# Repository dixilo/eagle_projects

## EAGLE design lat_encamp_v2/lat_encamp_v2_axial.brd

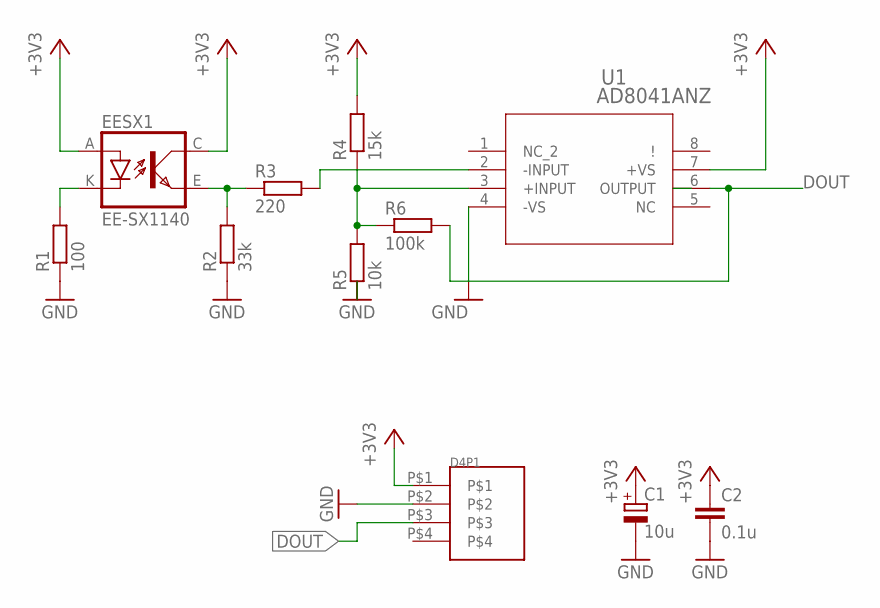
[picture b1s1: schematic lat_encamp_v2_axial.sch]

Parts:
C1: 10u; E2,5-6E
C2: 0.1u; C050-024X044
D4P1: DF1E-4P
EESX1: EE-SX1140
R1: 100; 0204/7
R2: 33k; 0204/7
R3: 220; 0204/7
R4: 15k; 0204/7
R5: 10k; 0204/7
R6: 100k; 0204/7
U1: AD8041ANZ; N_8_ADI

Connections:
+3V3: C1.+, C2.1, D4P1.P$1, EESX1.A, EESX1.C (COL), R4.2, U1.7 (+VS)
DOUT: D4P1.P$3, R6.2, U1.6 (OUTPUT)
GND: C1.-, C2.2, D4P1.P$2, R1.1, R2.1, R5.1, U1.4 (-VS)
unnamed: R3.2, U1.2 (-INPUT)
unnamed: R4.1, R5.2, R6.1, U1.3 (+INPUT)
unnamed: EESX1.E (EMIT), R2.2, R3.1
unnamed: EESX1.K (C), R1.2

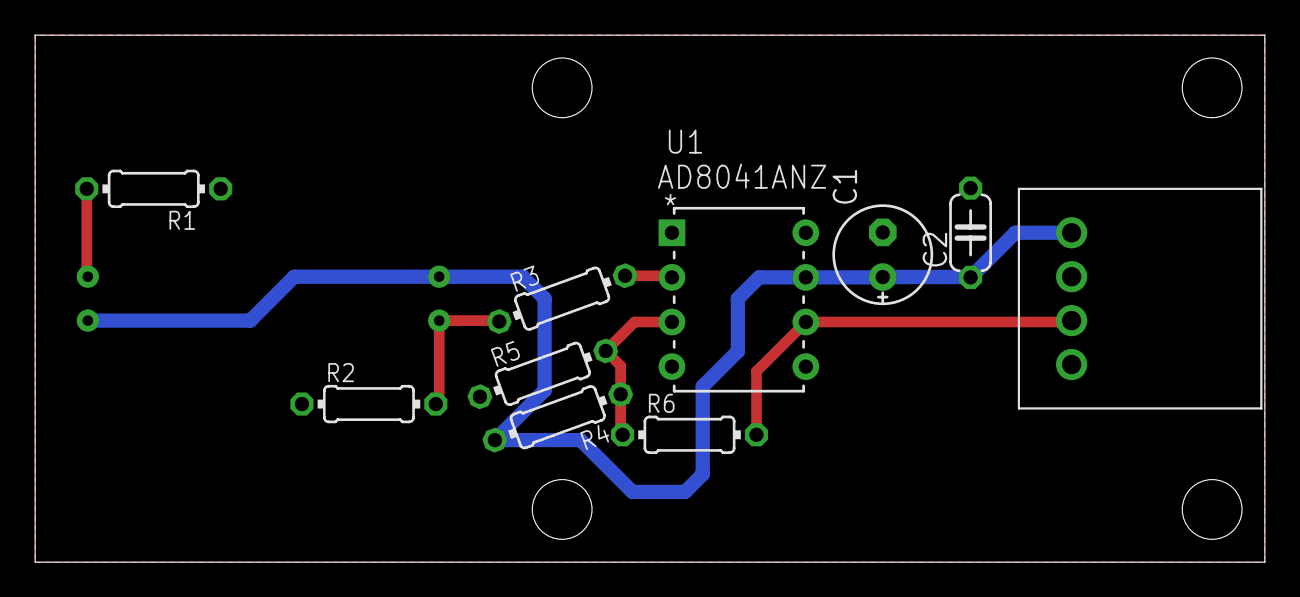
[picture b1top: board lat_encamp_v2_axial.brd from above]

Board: 2 copper layers, 70.0 x 30.0 mm, 11 parts (1 on the bottom side), 7 nets.

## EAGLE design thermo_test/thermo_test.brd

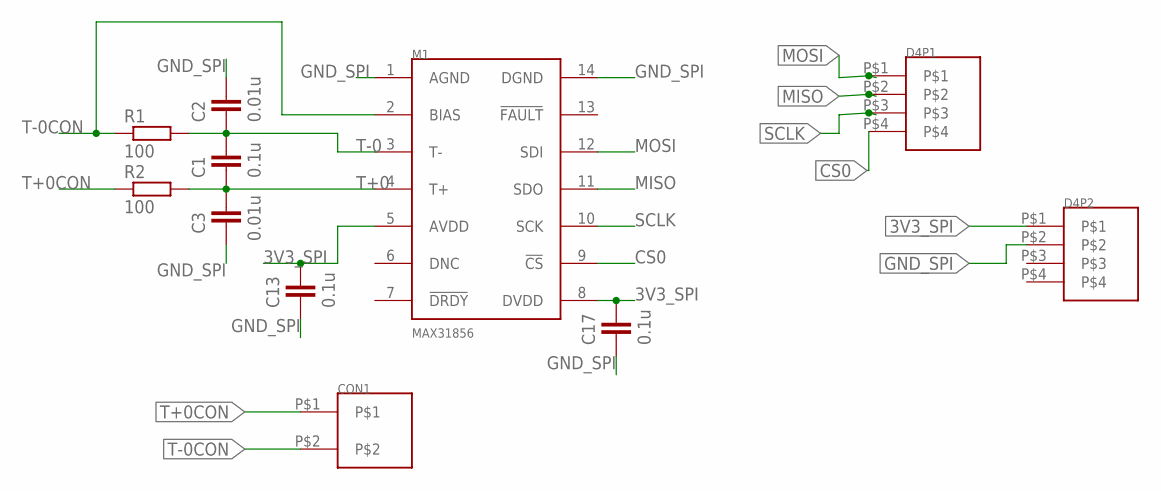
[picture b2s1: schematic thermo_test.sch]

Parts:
C1, C13, C17: 0.1u; C0603
C2, C3: 0.01u; C0603
CON1: 893-1332
D4P1, D4P2: DF1E-4P
M1: MAX31856; TSSOP14
R1, R2: 100; R0603

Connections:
3V3_SPI: C13.1, C17.1, D4P2.P$1, M1.5 (AVDD), M1.8 (DVDD)
CS0: D4P1.P$4, M1.9 (!CS)
GND_SPI: C2.1, C3.2, C13.2, C17.2, D4P2.P$2, M1.1 (AGND), M1.14 (DGND)
MISO: D4P1.P$2, M1.11 (SDO)
MOSI: D4P1.P$1, M1.12 (SDI)
SCLK: D4P1.P$3, M1.10 (SCK)
T+0: C1.2, C3.1, M1.4 (T+), R2.2
T+0CON: CON1.P$1, R2.1
T-0: C1.1, C2.2, M1.3 (T-), R1.2
T-0CON: CON1.P$2, M1.2 (BIAS), R1.1

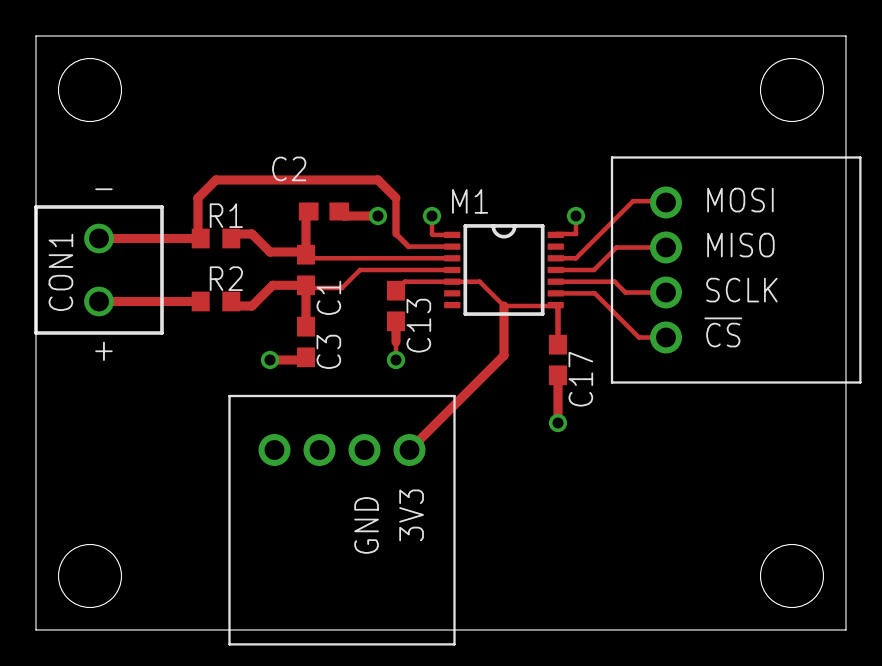
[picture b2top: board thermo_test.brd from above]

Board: 2 copper layers, 45.0 x 33.0 mm, 11 parts (0 on the bottom side), 10 nets.

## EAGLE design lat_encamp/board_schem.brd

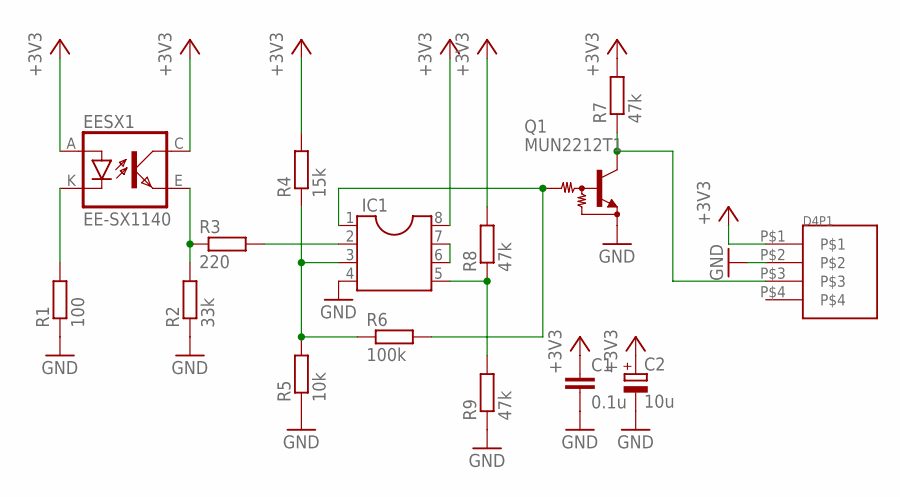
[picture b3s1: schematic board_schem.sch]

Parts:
C1: 0.1u; C050-024X044
C2: 10u; E2,5-5
D4P1: DF1E-4P
EESX1: EE-SX1140
IC1: DIL8; DIL08
Q1: MUN2212T1; SC59-BEC
R1: 100; 0207/10
R2: 33k; 0207/10
R3: 220; 0207/10
R4: 15k; 0207/10
R5: 10k; 0207/10
R6: 100k; 0207/10
R7, R8, R9: 47k; 0207/10

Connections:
+3V3: C1.1, C2.+, D4P1.P$1, EESX1.A, EESX1.C (COL), IC1.8, R4.2, R7.2, R8.2
GND: C1.2, C2.-, D4P1.P$2, IC1.4, Q1.E, R1.1, R2.1, R5.1, R9.1
unnamed: EESX1.K (C), R1.2
unnamed: EESX1.E (EMIT), R2.2, R3.1
unnamed: IC1.2, R3.2
unnamed: IC1.1, Q1.B, R6.2
unnamed: D4P1.P$3, Q1.C, R7.1
unnamed: IC1.3, R4.1, R5.2, R6.1
unnamed: IC1.6, IC1.7
unnamed: IC1.5, R8.1, R9.2

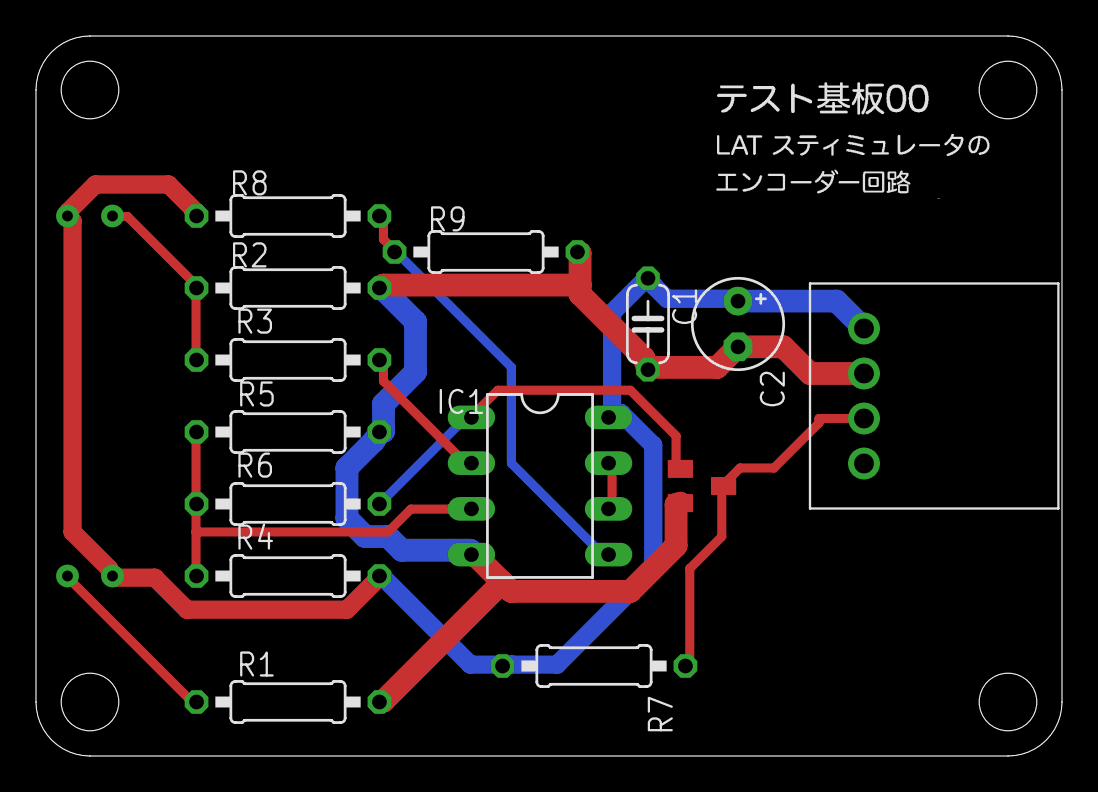
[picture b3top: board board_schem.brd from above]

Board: 2 copper layers, 57.0 x 40.0 mm, 15 parts (1 on the bottom side), 10 nets.

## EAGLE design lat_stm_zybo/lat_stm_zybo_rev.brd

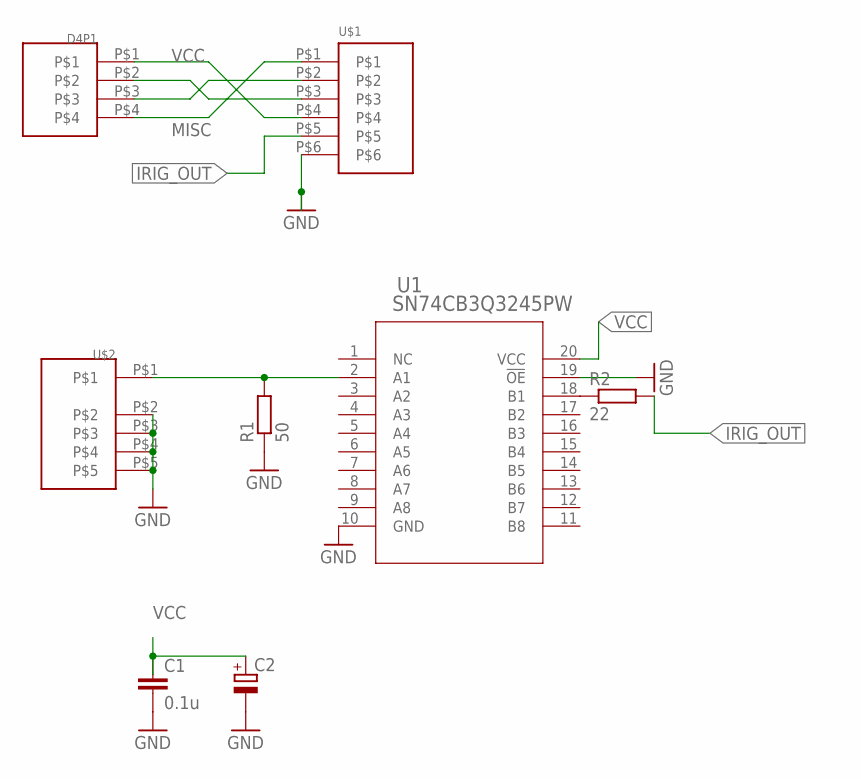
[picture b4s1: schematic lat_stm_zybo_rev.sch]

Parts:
C1: 0.1u; C0603
C2: CPOL-EUE2,5-6E; E2,5-6E
D4P1: DF1E-4P
R1: 50; R0603
R2: 22; R0603
U1: SN74CB3Q3245PW; PW20
U$1: DF1E-6P
U$2: 546-4049

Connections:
GND: C1.2, C2.-, R1.1, U1.10 (GND), U1.19 (!OE), U$1.P$6, U$2.P$2, U$2.P$3, U$2.P$4, U$2.P$5
IRIG_IN: R1.2, U1.2 (A1), U$2.P$1
IRIG_OUT: R2.2, U$1.P$5
MISC: D4P1.P$4, U$1.P$1
unnamed: R2.1, U1.18 (B1)
unnamed: D4P1.P$2, U$1.P$3
unnamed: D4P1.P$3, U$1.P$2
VCC: C1.1, C2.+, D4P1.P$1, U1.20 (VCC), U$1.P$4

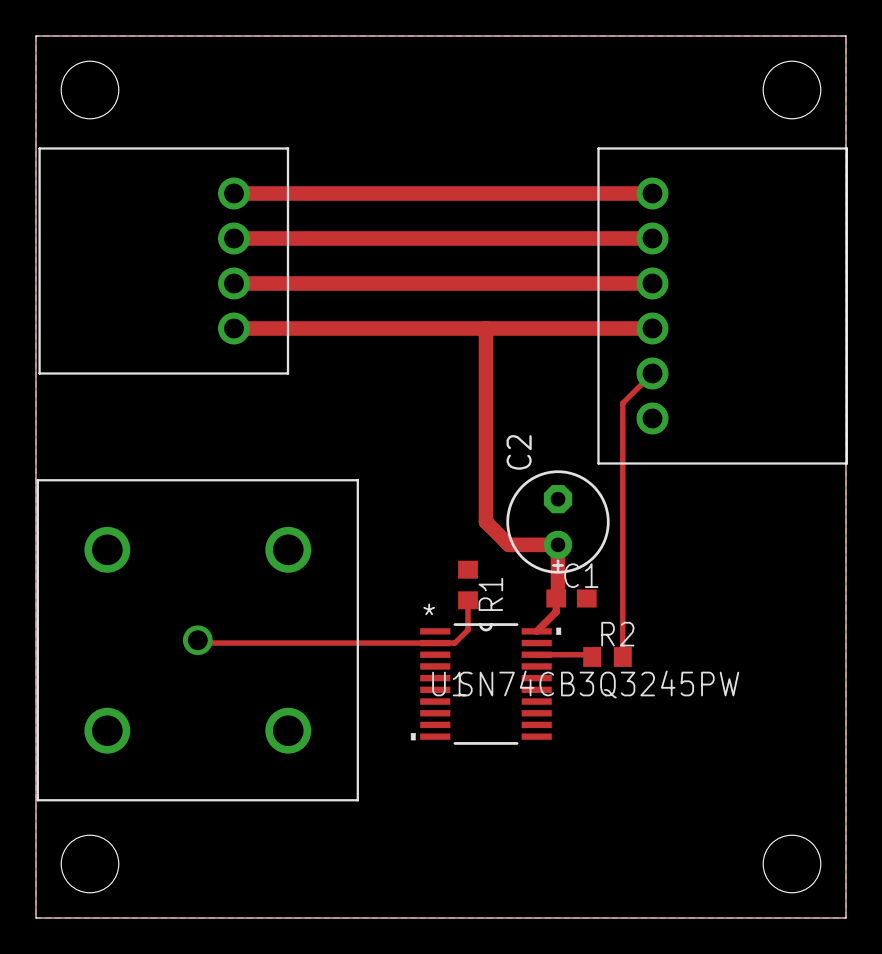
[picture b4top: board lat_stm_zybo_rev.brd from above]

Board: 2 copper layers, 45.0 x 49.0 mm, 8 parts (0 on the bottom side), 8 nets.

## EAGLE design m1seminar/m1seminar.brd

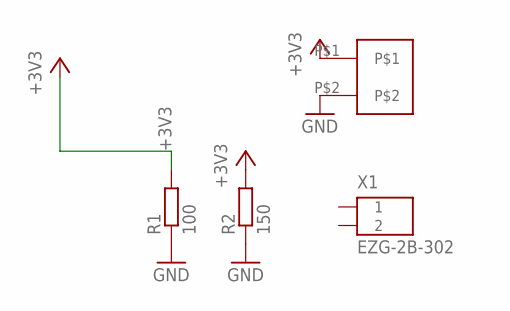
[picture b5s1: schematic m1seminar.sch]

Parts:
R1: 100; 0204/7
R2: 150; 0204/7
U$1: DF1E-2P
X1: EZG-2B-302; EZG-2B-2K-302

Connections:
+3V3: R1.2, R2.2, U$1.P$1
GND: R1.1, R2.1, U$1.P$2

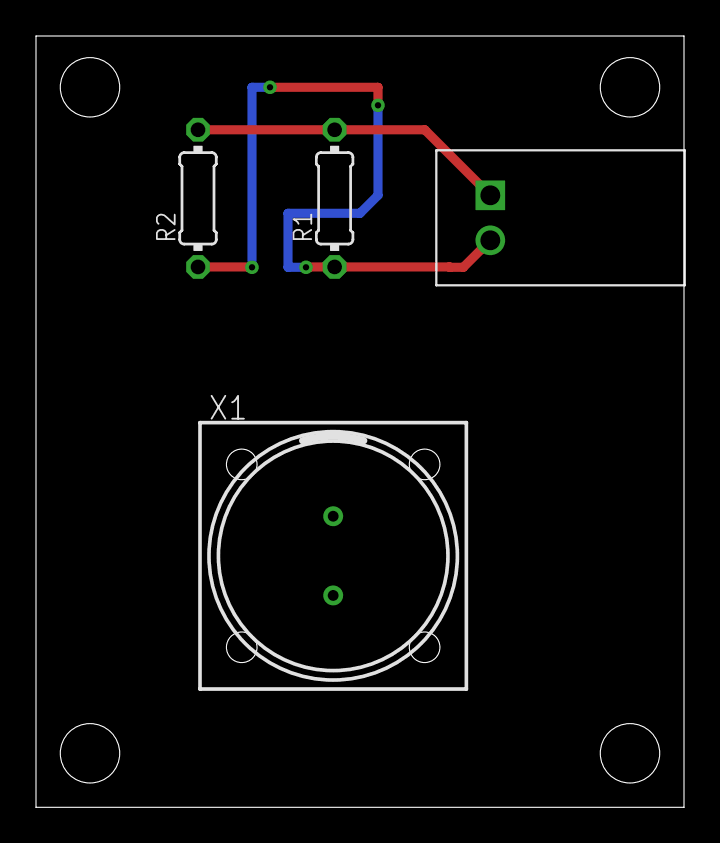
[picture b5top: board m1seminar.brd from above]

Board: 2 copper layers, 36.0 x 42.9 mm, 4 parts (0 on the bottom side), 2 nets.

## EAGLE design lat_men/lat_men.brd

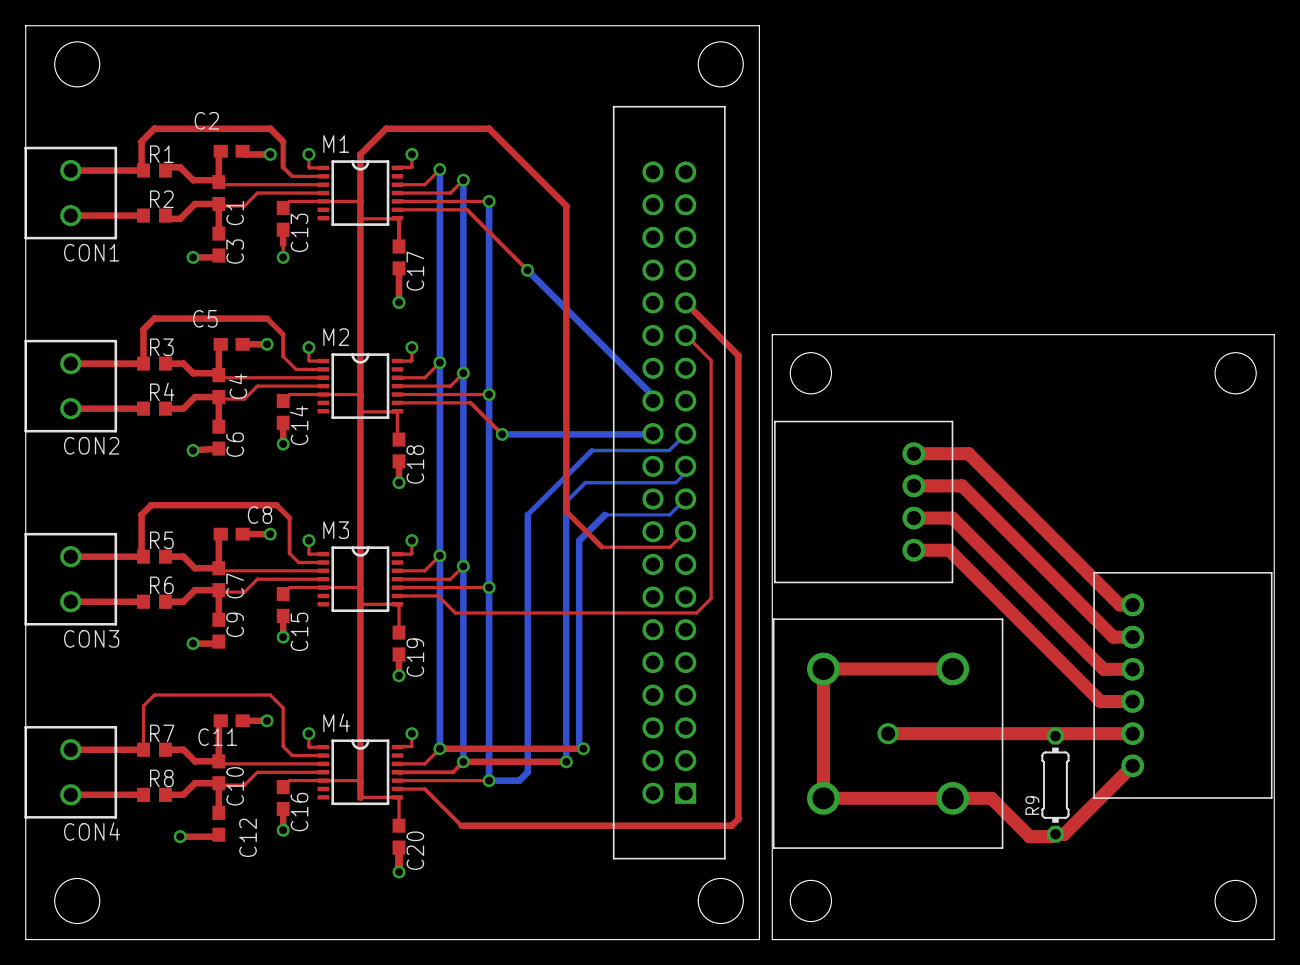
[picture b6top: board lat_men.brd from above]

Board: 2 copper layers, 97.0 x 71.0 mm, 41 parts (0 on the bottom side), 31 nets.

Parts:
C1, C4, C7, C10, C13, C14, C15, C16, C17, C18, C19, C20: 0.1u; C0603
C2, C3, C5, C6, C8, C9, C11, C12: 0.01u; C0603
CON1, CON2, CON3, CON4: 893-1332
D4P1: DF1E-4P
M1, M2, M3, M4: MAX31856; TSSOP14
R1, R2, R3, R4, R5, R6, R7, R8: 100; R0603
R9: 50; 0204/7
RPC1: RPI_CON
U$1: DF1E-6P
U$2: 546-4049

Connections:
3V3_SPI: C13.1, C14.1, C15.1, C16.1, C17.1, C18.1, C19.1, C20.1, M1.5, M1.8, M2.5, M2.8, M3.5, M3.8, M4.5, M4.8, RPC1.RPI17
CS0: M1.9, RPC1.RPI26
CS1: M2.9, RPC1.RPI24
CS2: M3.9, RPC1.RPI29
CS3: M4.9, RPC1.RPI31
GND_SPI: C2.1, C3.2, C5.1, C6.2, C8.1, C9.2, C11.1, C12.2, C13.2, C14.2, C15.2, C16.2, C17.2, C18.2, C19.2, C20.2, M1.1, M1.14, M2.1, M2.14, M3.1, M3.14, M4.1, M4.14, RPC1.RPI25
MISO: M1.11, M2.11, M3.11, M4.11, RPC1.RPI21
MOSI: M1.12, M2.12, M3.12, M4.12, RPC1.RPI19
unnamed: D4P1.P$1, U$1.P$4
unnamed: D4P1.P$2, U$1.P$3
unnamed: D4P1.P$3, U$1.P$2
unnamed: D4P1.P$4, U$1.P$1
unnamed: R9.2, U$1.P$5, U$2.P$1
unnamed: R9.1, U$1.P$6, U$2.P$2, U$2.P$3, U$2.P$4, U$2.P$5
SCLK: M1.10, M2.10, M3.10, M4.10, RPC1.RPI23
T+0: C1.2, C3.1, M1.4, R2.2
T+0CON: CON1.P$1, R2.1
T+1: C4.2, C6.1, M2.4, R4.2
T+1CON: CON2.P$1, R4.1
T+2: C7.2, C9.1, M3.4, R6.2
T+2CON: CON3.P$1, R6.1
T+3: C10.2, C12.1, M4.4, R8.2
T+3CON: CON4.P$1, R8.1
T-0: C1.1, C2.2, M1.3, R1.2
T-0CON: CON1.P$2, M1.2, R1.1
T-1: C4.1, C5.2, M2.3, R3.2
T-1CON: CON2.P$2, M2.2, R3.1
T-2: C7.1, C8.2, M3.3, R5.2
T-2CON: CON3.P$2, M3.2, R5.1
T-3: C10.1, C11.2, M4.3, R7.2
T-3CON: CON4.P$2, M4.2, R7.1

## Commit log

2021-07-15 files
2021-07-15 correction
2021-07-15 my library
